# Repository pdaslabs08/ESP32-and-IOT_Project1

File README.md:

# ESP32-and-IOT_Project1
Custom 4-layer ESP32 IoT PCB designed in KiCad with complete schematic, PCB layout, and manufacturing-ready files.

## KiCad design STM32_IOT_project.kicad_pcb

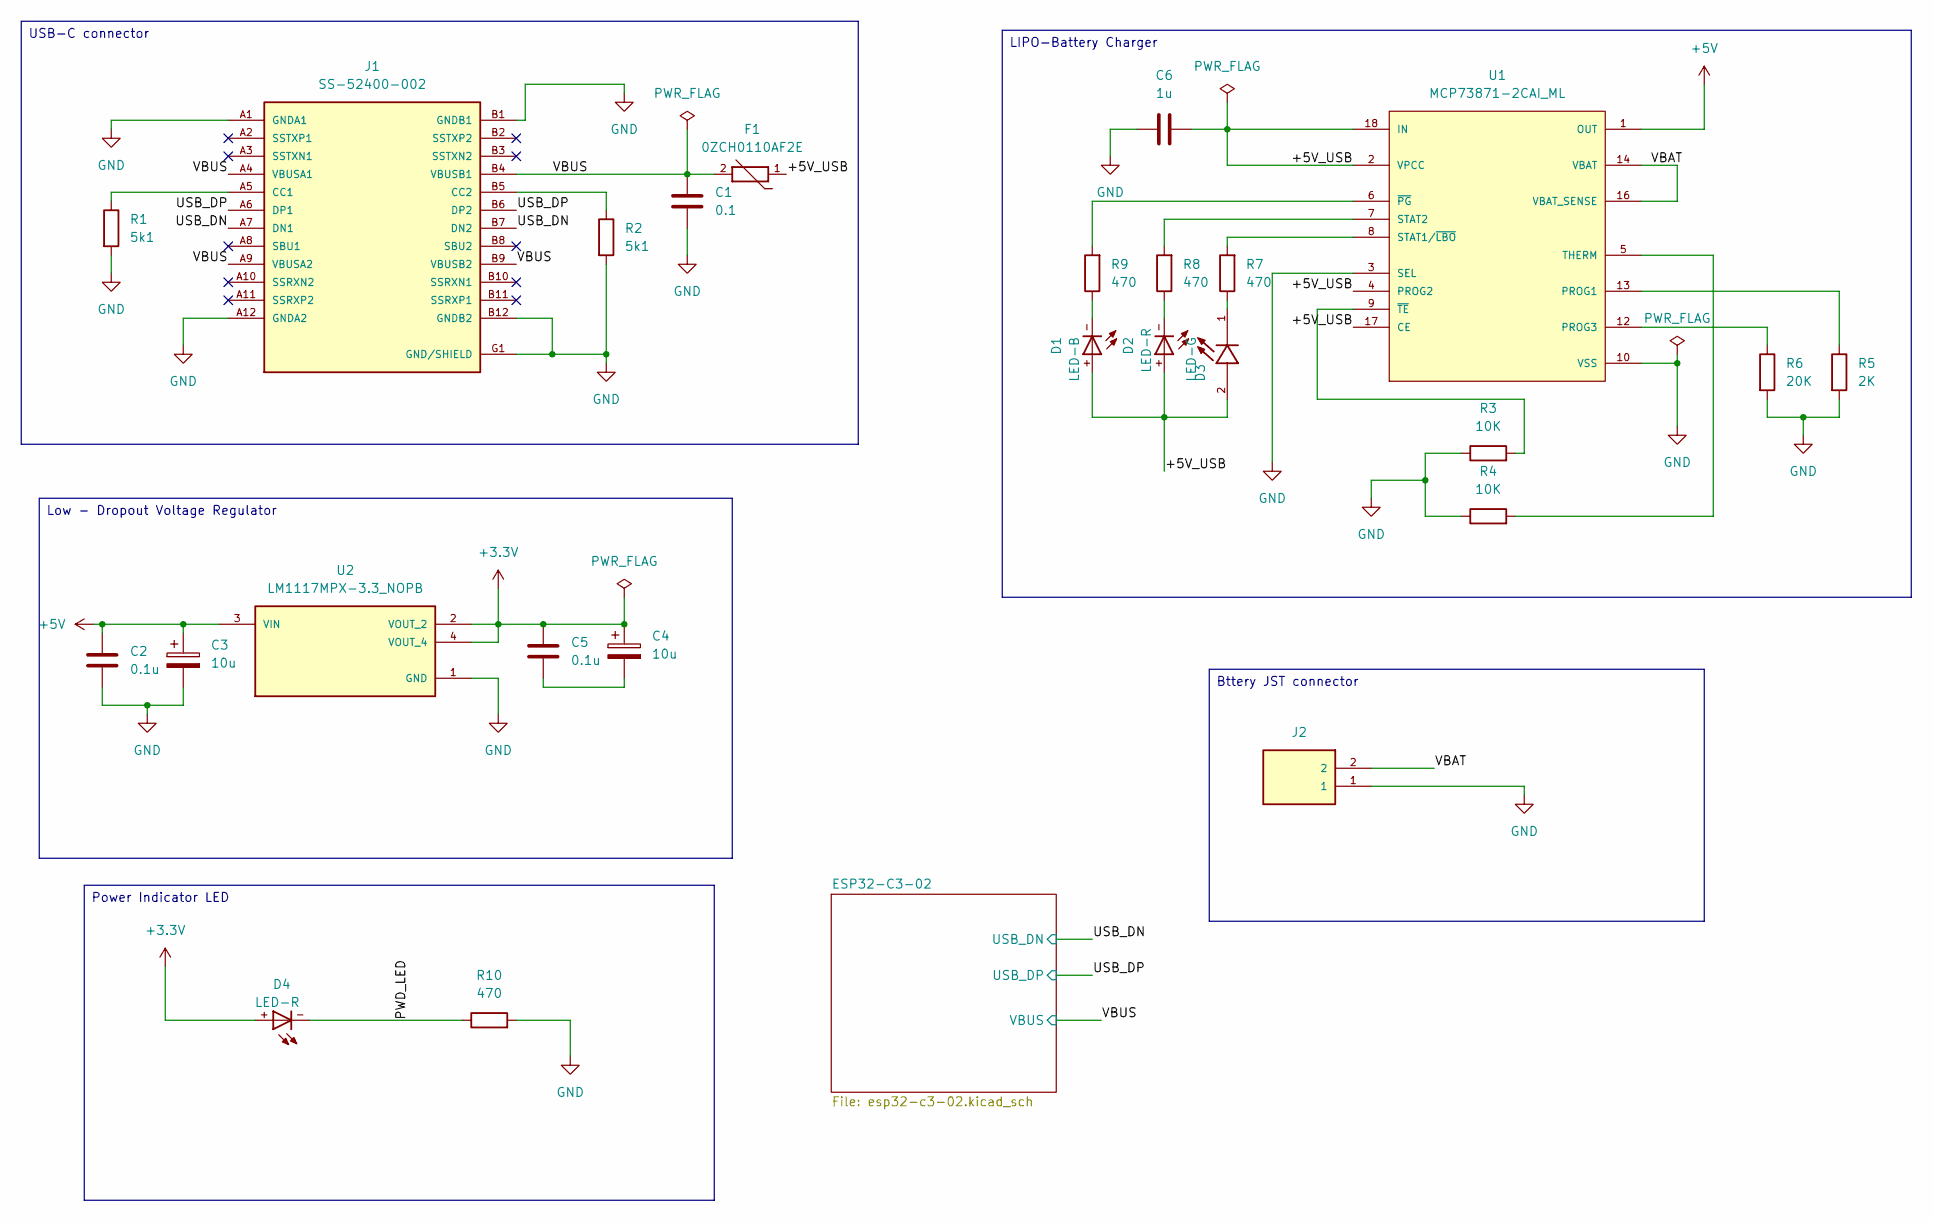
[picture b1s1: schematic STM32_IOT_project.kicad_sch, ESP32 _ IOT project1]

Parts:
C1: 0.1; C_0805_2012Metric
C2, C5: 0.1u; C_0805_2012Metric
C3, C4: 10u; CAPC3216X110N
C6: 1u; C_0805_2012Metric
D1: LED-B; DIOC200X125X110
D2, D4: LED-R; DIOC200X125X110
D3: LED-G; LED_LTST-C170GKT; PARTREV I
F1: 0ZCH0110AF2E; FUSC3225X100N; PARTREV Apr2023
J1: SS-52400-002; BELFUSE_SS-52400-002; PARTREV A0
J2: 177537-2; TE_177537-2; PARTREV R
R1, R2: 5k1; R_0805_2012Metric
R3, R4: 10K; R_0805_2012Metric
R5: 2K; R_0805_2012Metric
R6: 20K; R_0805_2012Metric
R7, R8, R9, R10: 470; R_0805_2012Metric
U1: MCP73871-2CAI_ML; QFN50P400X400X100-21N; PARTREV D
U2: LM1117MPX-3.3_NOPB; VREG_LM1117MPX-3.3_NOPB; PARTREV O

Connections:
+3.3V: C4.1, C5.1, D4.+, U2.2 (VOUT_2), U2.4 (VOUT_4); also elsewhere on the board
+5V: C2.1, C3.1, U1.1 (OUT), U1.20 (OUT), U2.3 (VIN)
/+5V_USB: C6.1, D1.+, D2.+, D3.2, F1.1, U1.2 (VPCC), U1.4 (PROG2), U1.17 (CE), U1.18 (IN), U1.19 (IN)
/PWD_LED: D4.-, R10.1
/USB_DN: J1.A7 (DN1), J1.B7 (DN2); also elsewhere on the board
/USB_DP: J1.A6 (DP1), J1.B6 (DP2); also elsewhere on the board
/VBAT: J2.2, U1.14 (VBAT), U1.15 (VBAT), U1.16 (VBAT_SENSE)
/VBUS: C1.1, F1.2, J1.A4 (VBUSA1), J1.A9 (VBUSA2), J1.B4 (VBUSB1), J1.B9 (VBUSB2); also elsewhere on the board
GND: C1.2, C2.2, C3.2, C6.2, J1.A1 (GNDA1), J1.A12 (GNDA2), J1.B1 (GNDB1), J1.B12 (GNDB2), J1.G1 (GND/SHIELD), J1.G2 (GND/SHIELD), J1.G3 (GND/SHIELD), J1.G4 (GND/SHIELD), J1.S1 (GND/SHIELD), J1.S2 (GND/SHIELD), J1.S3 (GND/SHIELD), J1.S4 (GND/SHIELD), J2.1, R1.2, R2.2, R3.1, R4.1, R5.2, R6.2, R10.2, U1.3 (SEL), U1.10 (VSS), U1.11 (VSS), U1.21 (VSS), U2.1 (GND); also elsewhere on the board
unnamed: C4.2, C5.2
unnamed: D1.-, R9.1
unnamed: D2.-, R8.1
unnamed: D3.1, R7.1
unnamed: J1.A5 (CC1), R1.1
unnamed: J1.B5 (CC2), R2.1
unnamed: R5.1, U1.13 (PROG1)
unnamed: R6.1, U1.12 (PROG3)
unnamed: R7.2, U1.8 (STAT1/~LBO)
unnamed: R8.2, U1.7 (STAT2)
unnamed: R4.2, U1.5 (THERM)
unnamed: R9.2, U1.6 (~PG)
unnamed: R3.2, U1.9 (~TE)

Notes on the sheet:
Bttery JST connector
USB-C connector
Low - Dropout Voltage Regulator
LIPO-Battery Charger
Power Indicator LED

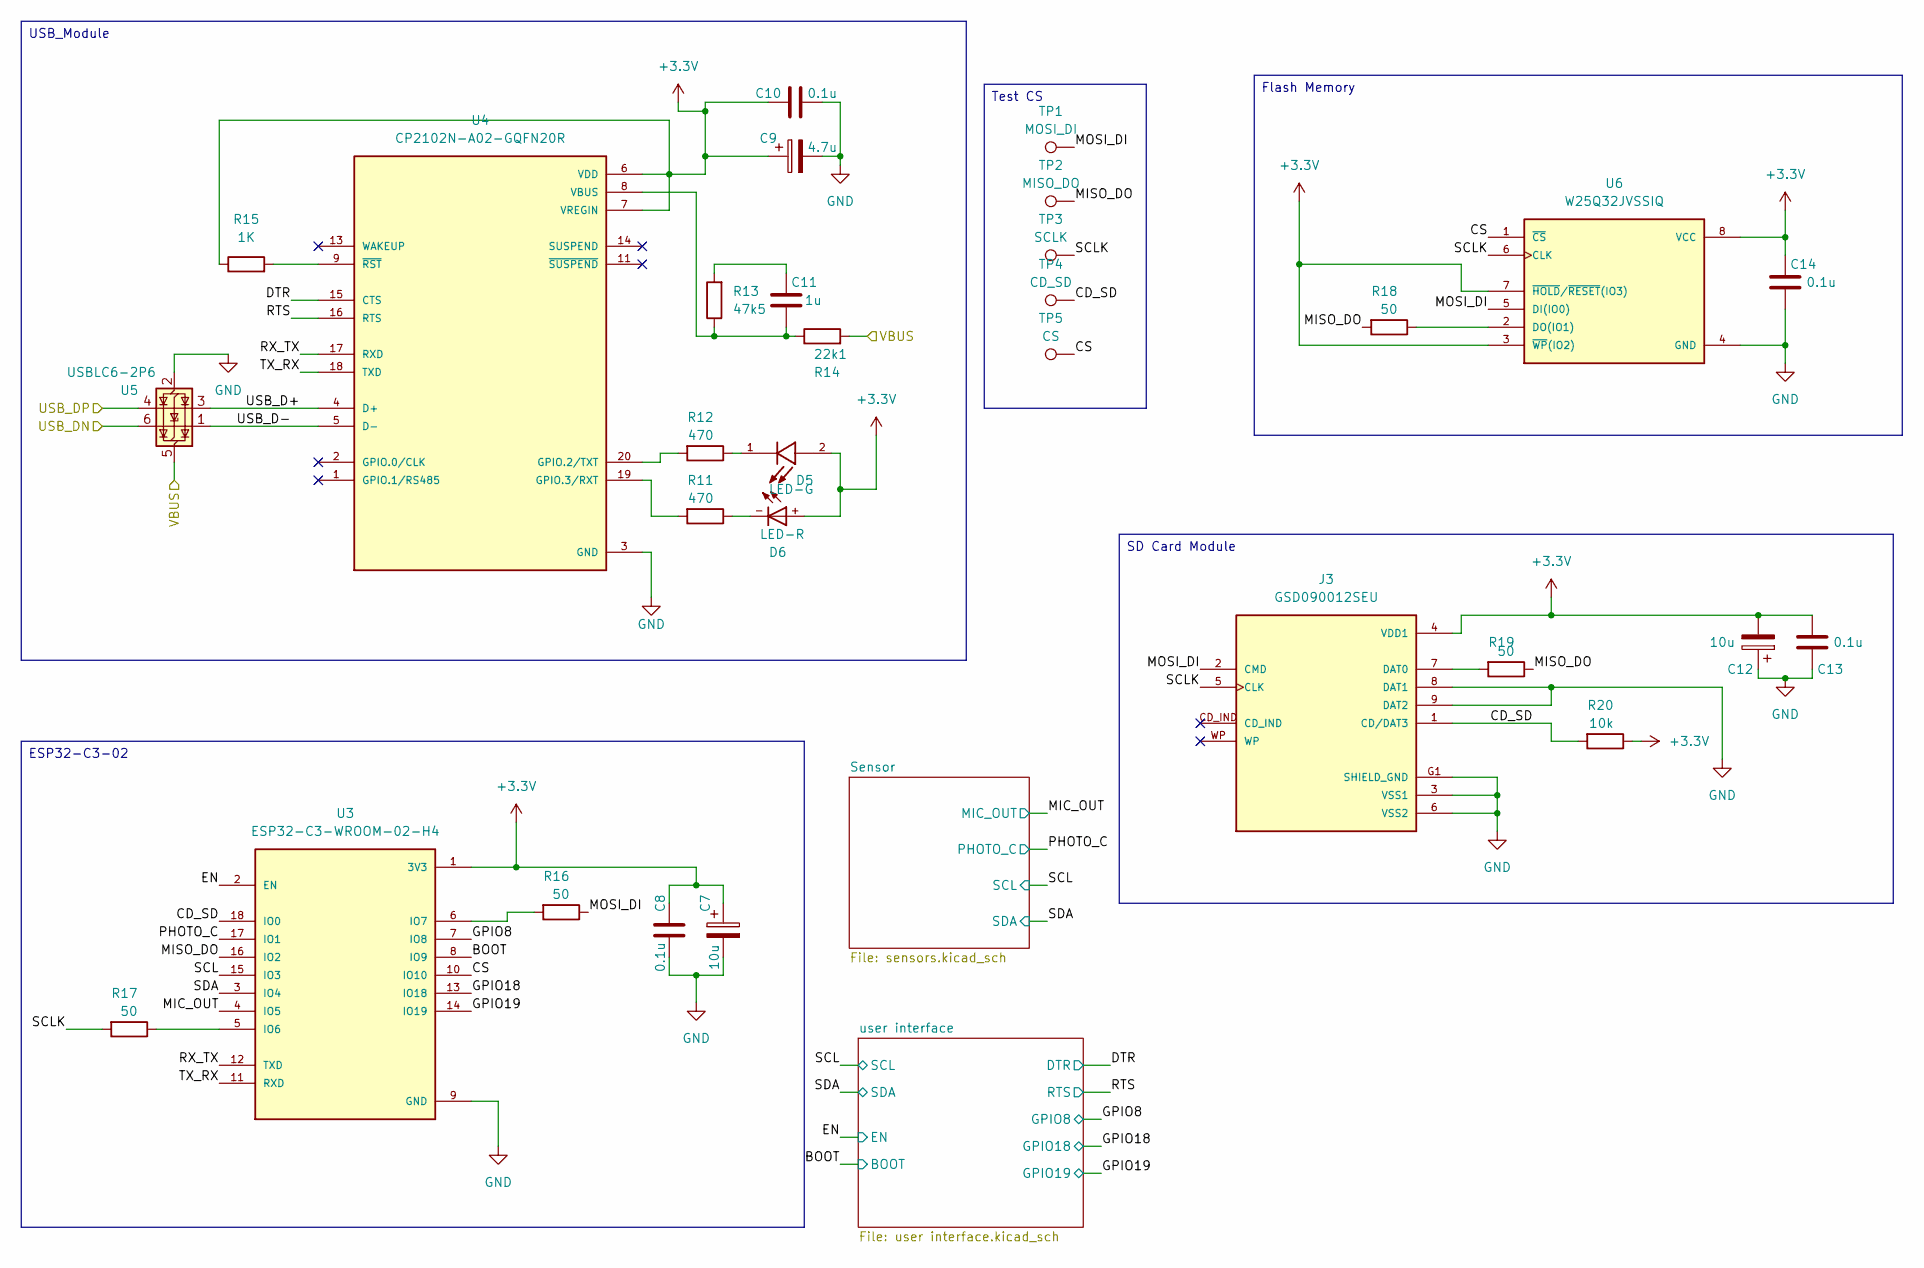
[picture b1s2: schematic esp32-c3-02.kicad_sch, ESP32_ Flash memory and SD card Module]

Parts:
C7, C12: 10u; CAPC3216X110N
C8, C10, C13, C14: 0.1u; C_0805_2012Metric
C9: 4.7u; CAPC3216X110N
C11: 1u; C_0805_2012Metric
D5: LED-G; LED_LTST-C170GKT; PARTREV I
D6: LED-R; DIOC200X125X110
J3: GSD090012SEU; AMPHENOL_GSD090012SEU; PARTREV E
R11, R12: 470; R_0805_2012Metric
R13: 47k5; R_0805_2012Metric
R14: 22k1; R_0805_2012Metric
R15: 1K; R_0805_2012Metric
R16, R17, R18, R19: 50; R_0805_2012Metric
R20: 10k; R_0805_2012Metric
TP1: MOSI_DI; TestPoint_Pad_D1.0mm
TP2: MISO_DO; TestPoint_Pad_D1.0mm
TP3: SCLK; TestPoint_Pad_D1.0mm
TP4: CD_SD; TestPoint_Pad_D1.0mm
TP5: CS; TestPoint_Pad_D1.0mm
U3: ESP32-C3-WROOM-02-H4; MODULE_ESP32-C3-WROOM-02-H4
U4: CP2102N-A02-GQFN20R; WFQFN-20; PARTREV 1.3
U5: USBLC6-2P6; SOT-666
U6: W25Q32JVSSIQ; SOIC127P790X216-8N; M_PART_NUMBER W25QXX

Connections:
+3.3V: C7.1, C8.1, C9.1, C10.1, C12.2, C13.2, C14.1, D5.2, D6.+, J3.4 (VDD1), R15.1, R20.1, U3.1 (3V3), U4.6 (VDD), U4.7 (VREGIN), U6.3 (~WP(IO2)), U6.7 (~HOLD/~RESET(IO3)), U6.8 (VCC); also elsewhere on the board
/ESP32-C3-02/BOOT: U3.8 (IO9); also elsewhere on the board
/ESP32-C3-02/CD_SD: J3.1 (CD/DAT3), R20.2, TP4.1, U3.18 (IO0)
/ESP32-C3-02/CS: TP5.1, U3.10 (IO10), U6.1 (~CS)
/ESP32-C3-02/DTR: U4.15 (CTS); also elsewhere on the board
/ESP32-C3-02/EN: U3.2 (EN); also elsewhere on the board
/ESP32-C3-02/GPIO8: U3.7 (IO8); also elsewhere on the board
/ESP32-C3-02/GPIO18: U3.13 (IO18); also elsewhere on the board
/ESP32-C3-02/GPIO19: U3.14 (IO19); also elsewhere on the board
/ESP32-C3-02/MIC_OUT: U3.4 (IO5); also elsewhere on the board
/ESP32-C3-02/MISO_DO: R18.2, R19.1, TP2.1, U3.16 (IO2)
/ESP32-C3-02/MOSI_DI: J3.2 (CMD), R16.1, TP1.1, U6.5 (DI(IO0))
/ESP32-C3-02/PHOTO_C: U3.17 (IO1); also elsewhere on the board
/ESP32-C3-02/RTS: U4.16 (RTS); also elsewhere on the board
/ESP32-C3-02/RX_TX: U3.12 (TXD), U4.17 (RXD)
/ESP32-C3-02/SCL: U3.15 (IO3); also elsewhere on the board
/ESP32-C3-02/SCLK: J3.5 (CLK), R17.2, TP3.1, U6.6 (CLK)
/ESP32-C3-02/SDA: U3.3 (IO4); also elsewhere on the board
/ESP32-C3-02/TX_RX: U3.11 (RXD), U4.18 (TXD)
/ESP32-C3-02/USB_D+: U4.4 (D+), U5.3 (I/O2)
/ESP32-C3-02/USB_D-: U4.5 (D-), U5.1 (I/O1)
/USB_DN: U5.6 (I/O1); also elsewhere on the board
/USB_DP: U5.4 (I/O2); also elsewhere on the board
/VBUS: R14.2, U5.5 (VBUS); also elsewhere on the board
GND: C7.2, C8.2, C9.2, C10.2, C12.1, C13.1, C14.2, J3.3 (VSS1), J3.6 (VSS2), J3.8 (DAT1), J3.9 (DAT2), J3.G1 (SHIELD_GND), J3.G2 (SHIELD_GND), J3.G3 (SHIELD_GND), J3.G4 (SHIELD_GND), U3.9 (GND), U3.19 (GND), U3.20 (GND), U3.21 (GND), U3.22 (GND), U3.23 (GND), U3.24 (GND), U3.25 (GND), U3.26 (GND), U3.27 (GND), U3.28 (GND), U3.29 (GND), U3.30 (GND), U3.31 (GND), U3.32 (GND), U3.33 (GND), U3.34 (GND), U3.35 (GND), U3.36 (GND), U3.37 (GND), U3.38 (GND), U3.39 (GND), U4.3 (GND), U4.12 (GND), U4.21 (GND), U4.EXP, U5.2 (GND), U6.4 (GND); also elsewhere on the board
unnamed: C11.2, R13.2
unnamed: D5.1, R12.1
unnamed: D6.-, R11.1
unnamed: J3.7 (DAT0), R19.2
unnamed: R17.1, U3.5 (IO6)
unnamed: R16.2, U3.6 (IO7)
unnamed: R12.2, U4.20 (GPIO.2/TXT)
unnamed: R11.2, U4.19 (GPIO.3/RXT)
unnamed: C11.1, R13.1, R14.1, U4.8 (VBUS)
unnamed: R15.2, U4.9 (~RST)
unnamed: R18.1, U6.2 (DO(IO1))

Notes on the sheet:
USB_Module
Flash Memory
Test CS
ESP32-C3-02
SD Card Module

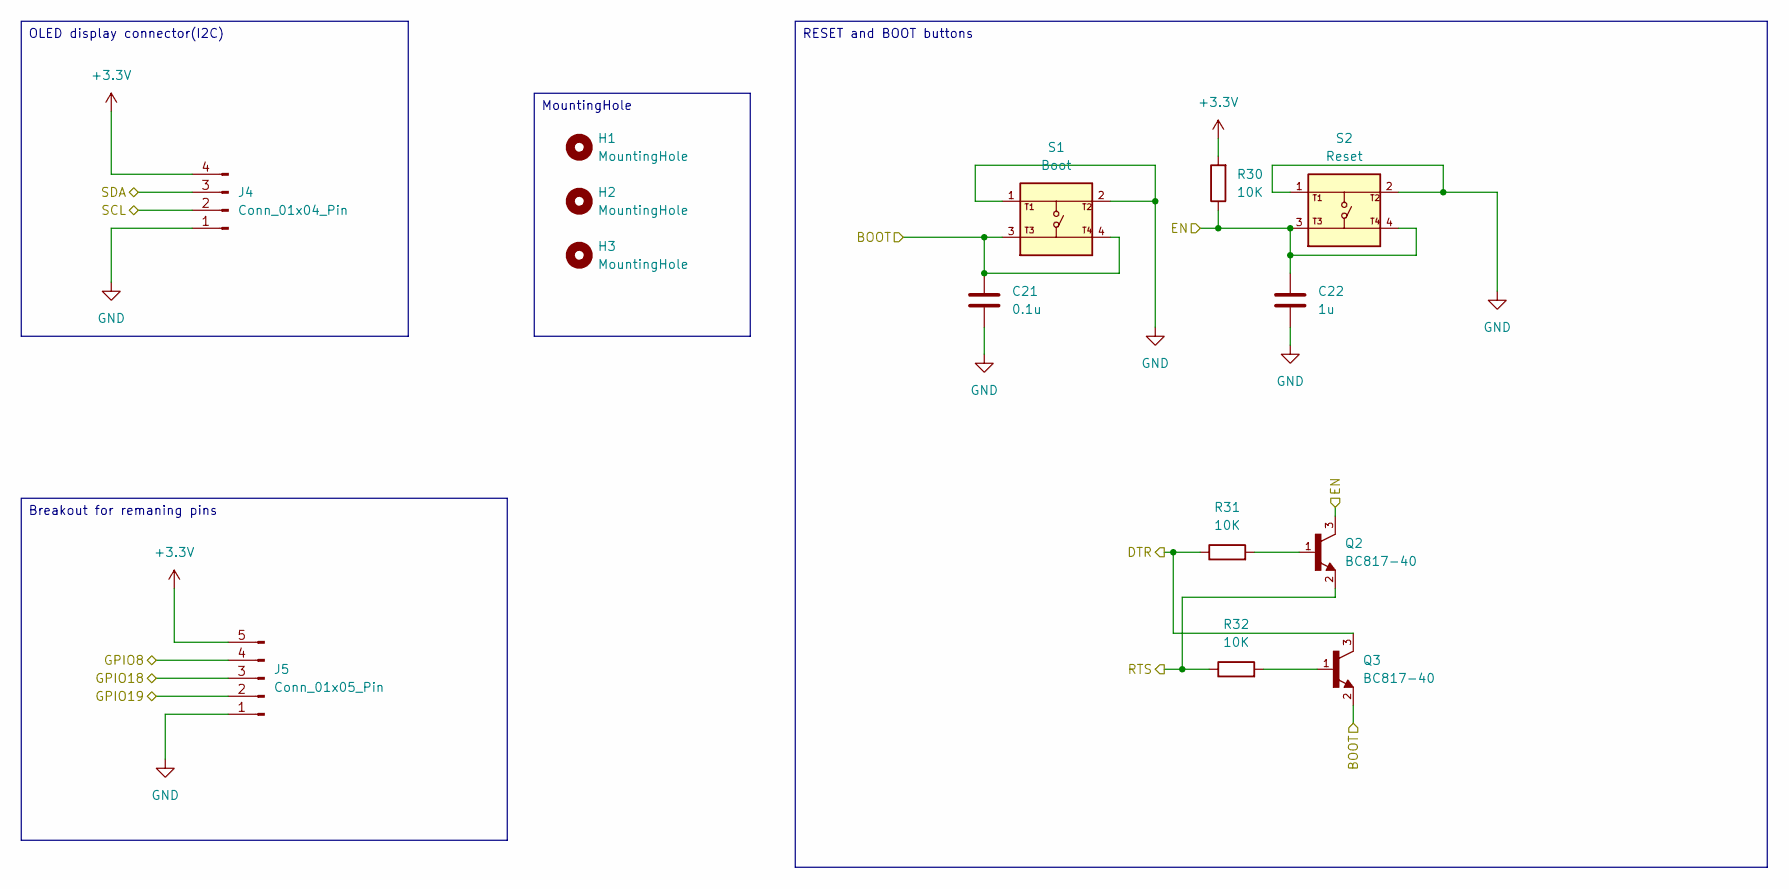
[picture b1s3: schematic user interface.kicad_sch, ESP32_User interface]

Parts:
C21: 0.1u; C_0805_2012Metric
C22: 1u; C_0805_2012Metric
H1, H2, H3: MountingHole; MountingHole_2.1mm
J4: Conn_01x04_Pin; PinHeader_1x04_P2.54mm_Vertical
J5: Conn_01x05_Pin; PinHeader_1x05_P2.54mm_Vertical
Q2, Q3: BC817-40; SOT95P240X120-3N; PARTREV 2023-08-16
R30, R31, R32: 10K; R_0805_2012Metric
S1: Boot; SW_USLPT2819DT2TR; PARTREV P
S2: Reset; SW_USLPT2819DT2TR; PARTREV P

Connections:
+3.3V: J4.4, J5.5, R30.2; also elsewhere on the board
/ESP32-C3-02/BOOT: C21.1, Q3.2, S1.3, S1.4; also elsewhere on the board
/ESP32-C3-02/DTR: Q3.3, R31.1; also elsewhere on the board
/ESP32-C3-02/EN: C22.1, Q2.3, R30.1, S2.3, S2.4; also elsewhere on the board
/ESP32-C3-02/GPIO8: J5.4; also elsewhere on the board
/ESP32-C3-02/GPIO18: J5.3; also elsewhere on the board
/ESP32-C3-02/GPIO19: J5.2; also elsewhere on the board
/ESP32-C3-02/RTS: Q2.2, R32.1; also elsewhere on the board
/ESP32-C3-02/SCL: J4.2; also elsewhere on the board
/ESP32-C3-02/SDA: J4.3; also elsewhere on the board
GND: C21.2, C22.2, J4.1, J5.1, S1.1, S1.2, S2.1, S2.2; also elsewhere on the board
unnamed: Q2.1, R31.2
unnamed: Q3.1, R32.2

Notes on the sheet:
OLED display connector(I2C)
Breakout for remaning pins
MountingHole
RESET and BOOT buttons

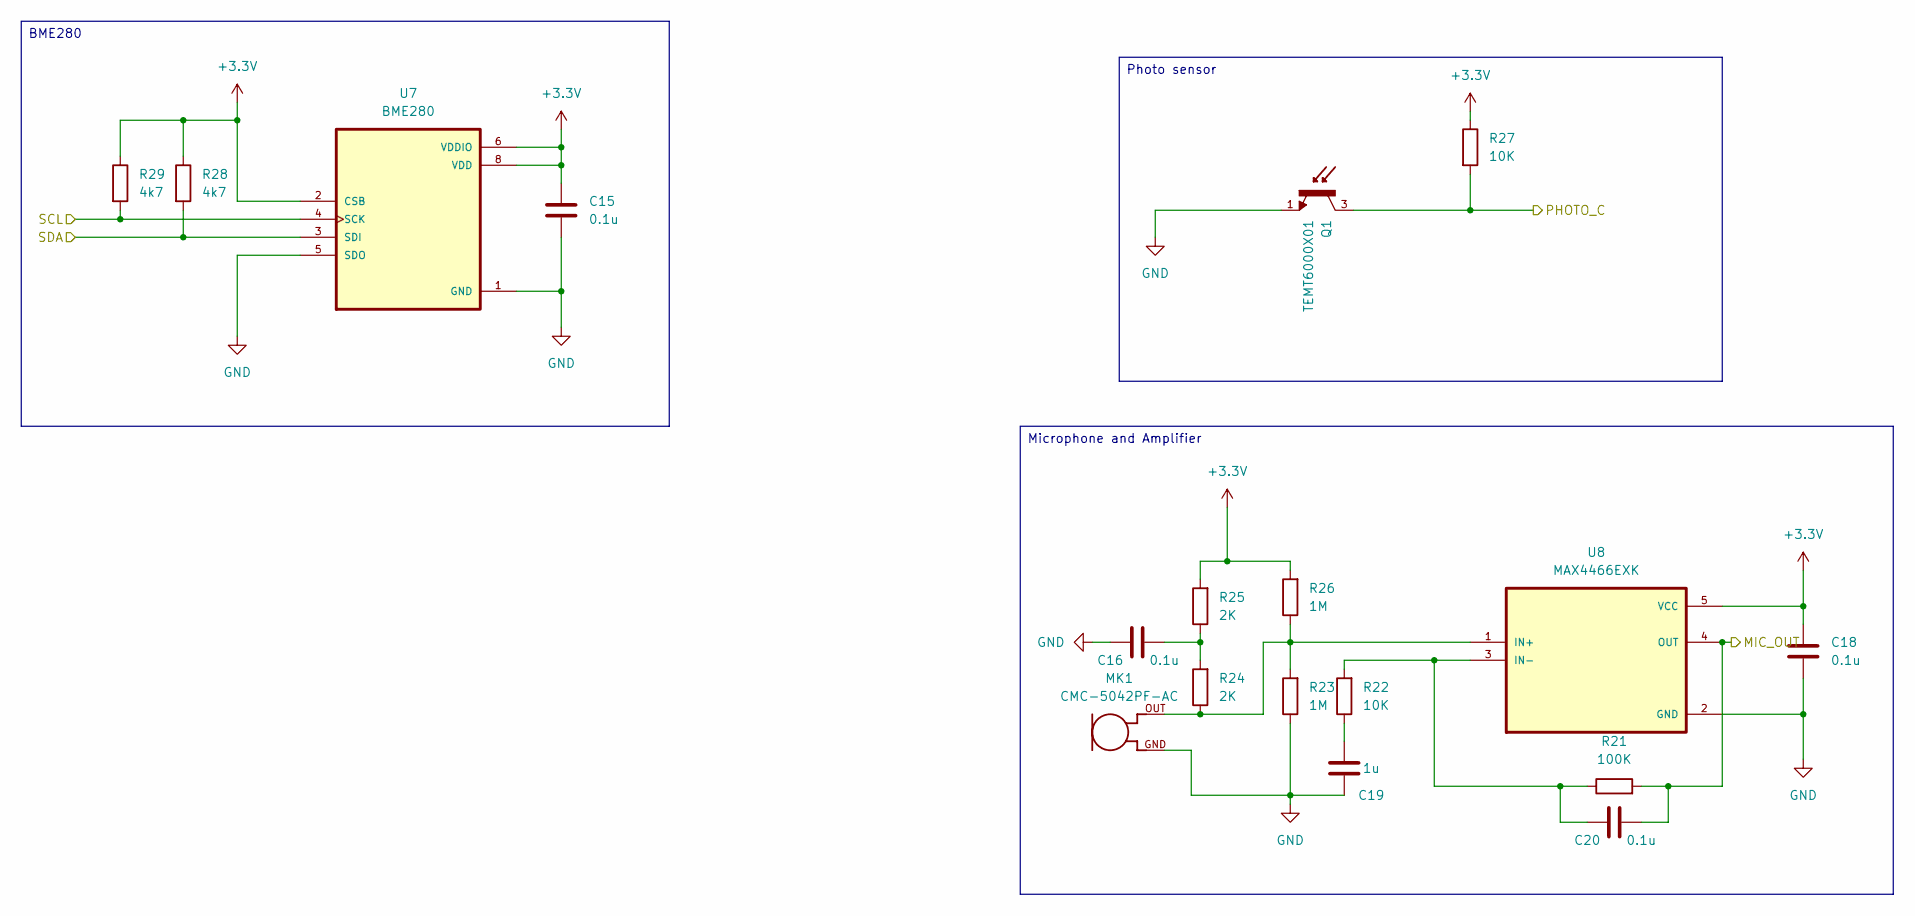
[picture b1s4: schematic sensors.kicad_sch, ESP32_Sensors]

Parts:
C15, C16, C18, C20: 0.1u; C_0805_2012Metric
C19: 1u; C_0805_2012Metric
MK1: CMC-5042PF-AC; CUI_CMC-5042PF-AC
Q1: TEMT6000X01; TRANS_TEMT6000X01; PARTREV 1.9
R21: 100K; R_0805_2012Metric
R22, R27: 10K; R_0805_2012Metric
R23, R26: 1M; R_0805_2012Metric
R24, R25: 2K; R_0805_2012Metric
R28, R29: 4k7; R_0805_2012Metric
U7: BME280; PSON65P250X250X100-8N
U8: MAX4466EXK; SOT65P210X110-5N

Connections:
+3.3V: C15.1, C18.1, R25.2, R26.2, R27.1, R28.1, R29.1, U7.2 (CSB), U7.6 (VDDIO), U7.8 (VDD), U8.5 (VCC); also elsewhere on the board
/ESP32-C3-02/MIC_OUT: C20.2, R21.2, U8.4 (OUT); also elsewhere on the board
/ESP32-C3-02/PHOTO_C: Q1.3, R27.2; also elsewhere on the board
/ESP32-C3-02/SCL: R29.2, U7.4 (SCK); also elsewhere on the board
/ESP32-C3-02/SDA: R28.2, U7.3 (SDI); also elsewhere on the board
GND: C15.2, C16.1, C18.2, C19.1, MK1.GND, Q1.1, R23.1, U7.1 (GND), U7.5 (SDO), U7.7 (GND), U8.2 (GND); also elsewhere on the board
unnamed: C16.2, R24.2, R25.1
unnamed: C19.2, R22.1
unnamed: MK1.OUT, R23.2, R24.1, R26.1, U8.1 (IN+)
unnamed: C20.1, R21.1, R22.2, U8.3 (IN-)

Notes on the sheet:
Photo sensor
BME280
Microphone and Amplifier

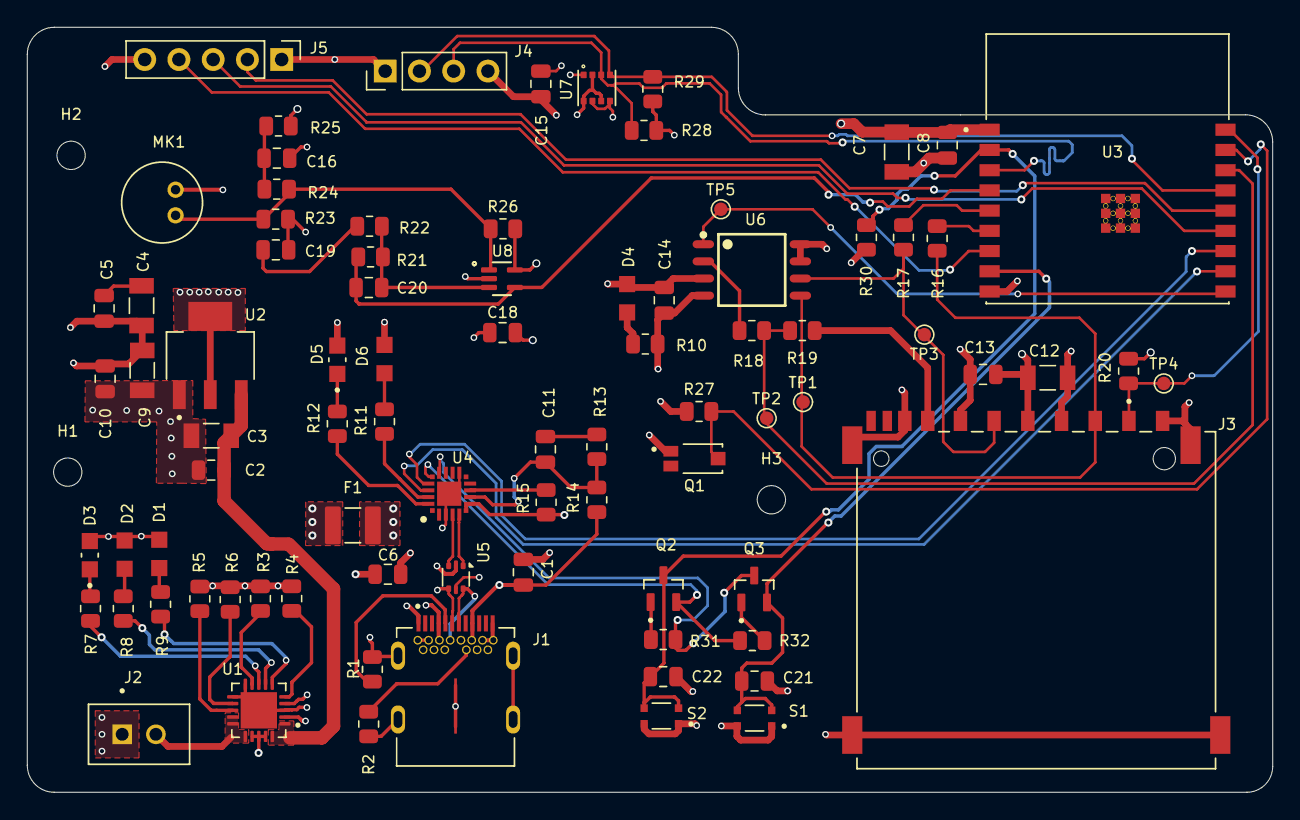
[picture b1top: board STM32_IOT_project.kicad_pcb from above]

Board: 4 copper layers, 92.4 x 56.8 mm, 87 parts (0 on the bottom side), 59 nets.
